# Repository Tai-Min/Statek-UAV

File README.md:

# Statek-UAV
ROS based UAV, Master's degree final project.

This repository consists of CAD files for the chassis, CAD files for electronic boards, catkin workspace for all ROS nodes created for the project and some additional scripts used during development.

The core part of this project is the real, 3D printed vehicle along with all the hardware attached to it (Jetson Nano B01 for main controller and STM32f103RBT6 for real time core). 

The software part of this project can be split into real time (closed loop wheel control), short term navigation (movement between two GPS waypoints) and long term navigation (navigation through series of GPS waypoints).
During the project's development, my main focus was on short term navigation, which is also the biggest and most complicated part of the project. Short term navigation stack
consists of static local map generator, dynamic local map generator (human leg detector mostly based on U-Net fully convolutional neural network), Voronoi graph generator, A* path planner and non linear model predictive controller for navigation.

For more info see [this arcitle](https://www.hackster.io/Tai-Min/statek-uav-ff225e).

**Just to warn you:** If you want to use this project somehow, use it as reference only. It is NOT meant to be assembled as it contains some design flaws both in hardware
and software that I don't intent to fix in this iteration of the project as code in this repository will stay in unchanged since the moment I handed over my thesis.
Most of the files in the "instructions" folder consists of the steps I've did to setup my hardware and Ipopt solver. Those might not work for you/could be dangerous (I might've abused sudo a bit) so use them at your own risk. The code quality depends on the time I had untill the deadline to hand over my thesis. In my opinion it should be fine for the most part, well documented and easy to follow but judge for yourself.

**Disclaimer:** I've tried to credit all authors of 3D files used in the project. All of the models had permissive license allowing me to use them.
If you see your work here without being credited or you just don't want to have your files used here - open an issue on this project and I'll fix any problems.

The files in this folder have the following structure:
* CAD
  * detailed - Inventor files for the 3D printing and assembling.
  * low_poly - Inventor files for simple low poly model for Gazebo and Rviz.
* catkin_ws/src
  * statek - Metapackage for the project
  * statek_calibrate - Calibration algorithms for cameras, GPS Kalman filter, IMU, Motor's PI controller autotuning. 
  * statek_config - Config files for the robot, including transformations, urdf and parameters for ROS nodes.
  * statek_hw - code to launch hardware based nodes (lidar, rosserial, cameras etc.) along with source code for real time controller.
  * statek_map - Mapping algorithms (dynamic local mapper, voronoi generator and GPS to hyperplane casting).
  * statek_ml - Leg detector based mostly on U-net fully convolutional neural network
  * statek_nav - Navigation algorithms (NMPC and GPS waypoint follower script).
  * statek_plan - A* path planner for short term navigation.
  * statek_playground - Simple launch nodes to play with the hardware.
  * statek_rviz - Rviz visualization files.
  * statek_sim - Gazebo simulation files.
  * statek_srv - Server files to communicate with web application (really rough draft).
  * statek_teleop - Teleoperation nodes for Dualshock 4 gamepad.
* electronics
  * AM4096_encoder - KiCad's files for AM4096 encoder board.
  * Nucleo_screw_shield - KiCad's files for screw shield that fits morpho connector.
  * button_panel - Unused in the project.
  * connections - Electrical connections of the project.
* instructions - Rough draft of what I did to setup the robot.
* media - Contains camera's calibration chessboard.
* thesis_scripts - Some files used to add more value to the project.

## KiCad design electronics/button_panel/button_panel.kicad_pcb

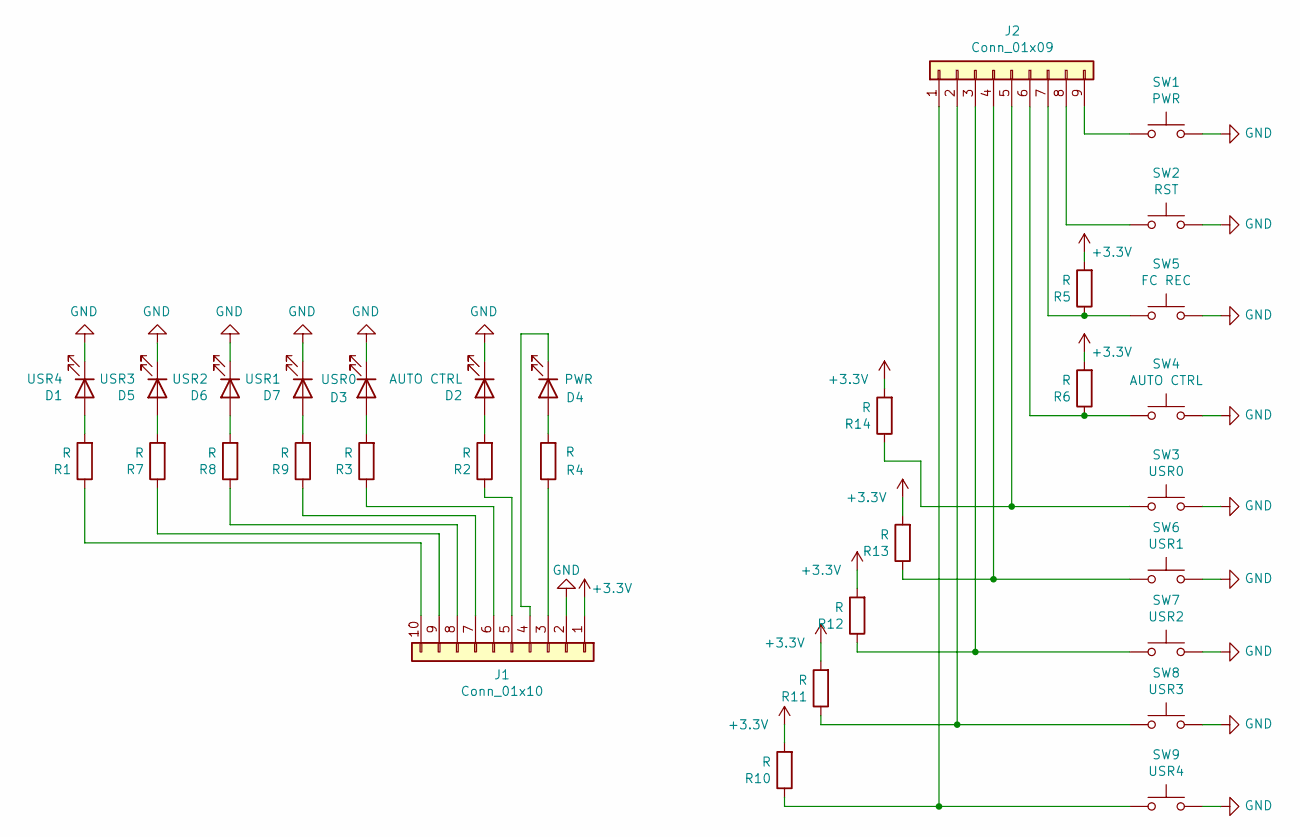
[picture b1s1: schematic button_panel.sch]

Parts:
D1: USR4; LED_D5.0mm_Clear
D2: AUTO CTRL; LED_D5.0mm_Clear
D3: USR0; LED_D5.0mm_Clear
D4: PWR; LED_D5.0mm_Clear
D5: USR3; LED_D5.0mm_Clear
D6: USR2; LED_D5.0mm_Clear
D7: USR1; LED_D5.0mm_Clear
J1: Conn_01x10; PinHeader_1x10_P2.54mm_Vertical
J2: Conn_01x09; PinHeader_1x09_P2.54mm_Vertical
R1, R2, R3, R4, R5, R6, R7, R8, R9, R10, R11, R12, R13, R14: R; R_1206_3216Metric_Pad1.42x1.75mm_HandSolder
SW1: PWR; SW_PUSH_6mm
SW2: RST; SW_PUSH_6mm
SW3: USR0; SW_PUSH_6mm
SW4: AUTO CTRL; SW_PUSH_6mm
SW5: FC REC; SW_PUSH_6mm
SW6: USR1; SW_PUSH_6mm
SW7: USR2; SW_PUSH_6mm
SW8: USR3; SW_PUSH_6mm
SW9: USR4; SW_PUSH_6mm

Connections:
+3V3: J1.1, R5.2, R6.2, R10.2, R11.2, R12.2, R13.2, R14.2
GND: D1.1 (K), D2.1 (K), D3.1 (K), D5.1 (K), D6.1 (K), D7.1 (K), J1.2, SW1.2, SW2.2, SW3.2, SW4.2, SW5.2, SW6.2, SW7.2, SW8.2, SW9.2
unnamed: D1.2 (A), R1.2
unnamed: D2.2 (A), R2.2
unnamed: D3.2 (A), R3.2
unnamed: D4.1 (K), J1.4
unnamed: D4.2 (A), R4.2
unnamed: D5.2 (A), R7.2
unnamed: D6.2 (A), R8.2
unnamed: D7.2 (A), R9.2
unnamed: J1.3, R4.1
unnamed: J1.5, R2.1
unnamed: J1.6, R3.1
unnamed: J1.7, R9.1
unnamed: J1.8, R8.1
unnamed: J1.9, R7.1
unnamed: J1.10, R1.1
unnamed: J2.1, R10.1, SW9.1
unnamed: J2.2, R11.1, SW8.1
unnamed: J2.3, R12.1, SW7.1
unnamed: J2.4, R13.1, SW6.1
unnamed: J2.5, R14.1, SW3.1
unnamed: J2.6, R6.1, SW4.1
unnamed: J2.7, R5.1, SW5.1
unnamed: J2.8, SW2.1
unnamed: J2.9, SW1.1

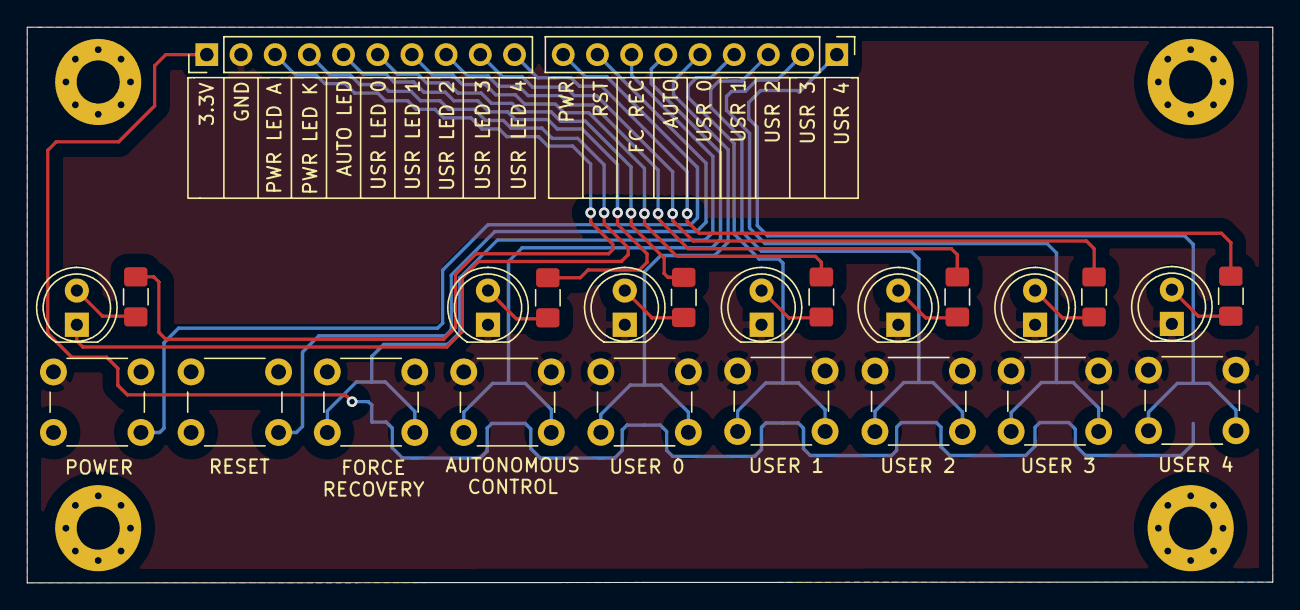
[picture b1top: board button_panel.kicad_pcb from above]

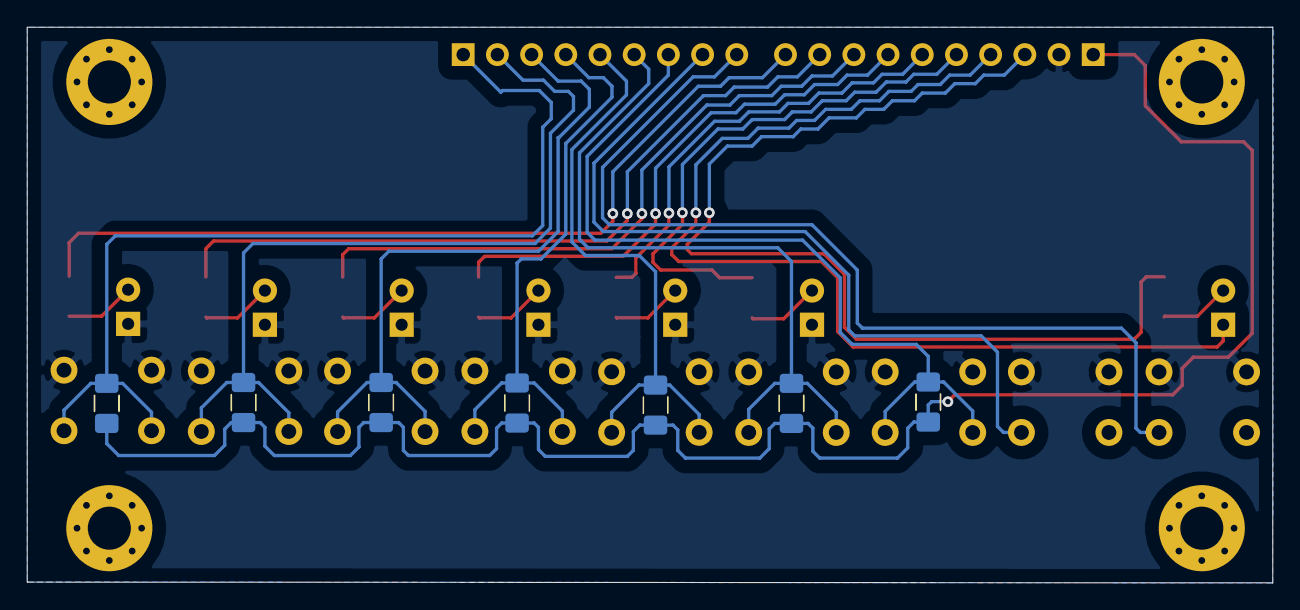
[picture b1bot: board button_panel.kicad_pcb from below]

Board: 2 copper layers, 92.5 x 41.3 mm, 32 parts (7 on the bottom side), 26 nets.

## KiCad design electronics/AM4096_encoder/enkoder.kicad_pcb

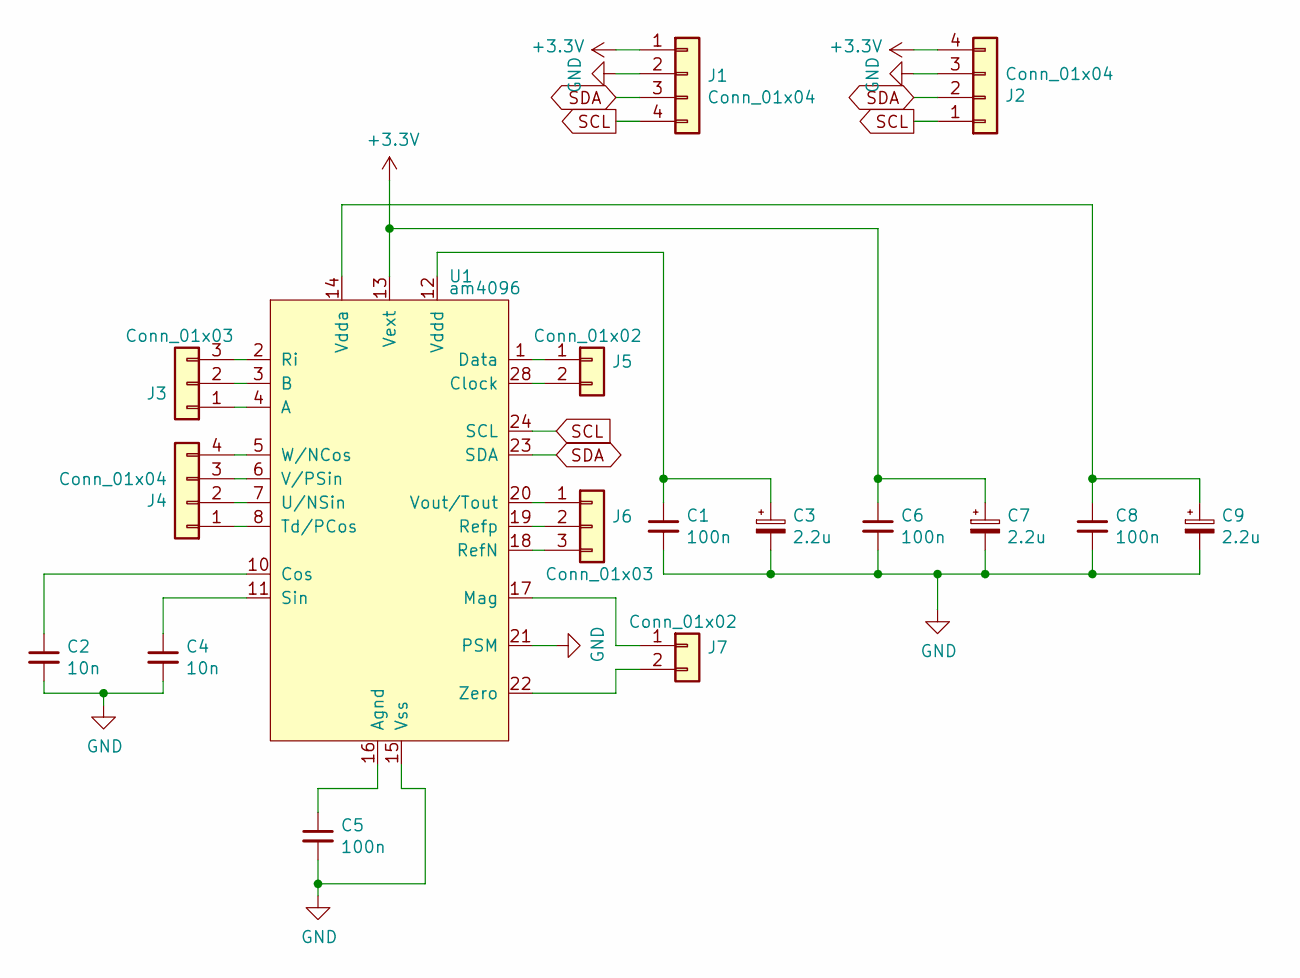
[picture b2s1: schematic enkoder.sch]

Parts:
C1, C5, C6, C8: 100n; C_1206_3216Metric_Pad1.42x1.75mm_HandSolder
C2, C4: 10n; C_1206_3216Metric_Pad1.42x1.75mm_HandSolder
C3, C7, C9: 2.2u; CP_EIA-3216-18_Kemet-A_Pad1.58x1.35mm_HandSolder
J1, J4: Conn_01x04; PinSocket_1x04_P2.54mm_Vertical
J2: Conn_01x04; TerminalBlock_MetzConnect_Type086_RT03404HBLC_1x04_P3.81mm_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
J3, J6: Conn_01x03; PinSocket_1x03_P2.54mm_Vertical
J5, J7: Conn_01x02; PinSocket_1x02_P2.54mm_Vertical
U1: am4096; SSOP-28_5.3x10.2mm_P0.65mm

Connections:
+3V3: C6.1, C7.1, J1.1, J2.4, U1.13 (Vext)
GND: C1.2, C2.2, C3.2, C4.2, C5.2, C6.2, C7.2, C8.2, C9.2, J1.2, J2.3, U1.15 (Vss), U1.21 (PSM)
unnamed: C1.1, C3.1, U1.12 (Vddd)
unnamed: C2.1, U1.10 (Cos)
unnamed: C4.1, U1.11 (Sin)
unnamed: C5.1, U1.16 (Agnd)
unnamed: C8.1, C9.1, U1.14 (Vdda)
unnamed: J3.1, U1.4 (A)
unnamed: J3.2, U1.3 (B)
unnamed: J3.3, U1.2 (Ri)
unnamed: J4.1, U1.8 (Td/PCos)
unnamed: J4.2, U1.7 (U/NSin)
unnamed: J4.3, U1.6 (V/PSin)
unnamed: J4.4, U1.5 (W/NCos)
unnamed: J5.1, U1.1 (Data)
unnamed: J5.2, U1.28 (Clock)
unnamed: J6.1, U1.20 (Vout/Tout)
unnamed: J6.2, U1.19 (Refp)
unnamed: J6.3, U1.18 (RefN)
unnamed: J7.1, U1.17 (Mag)
unnamed: J7.2, U1.22 (Zero)
SCL: J1.4, J2.1, U1.24 (SCL)
SDA: J1.3, J2.2, U1.23 (SDA)

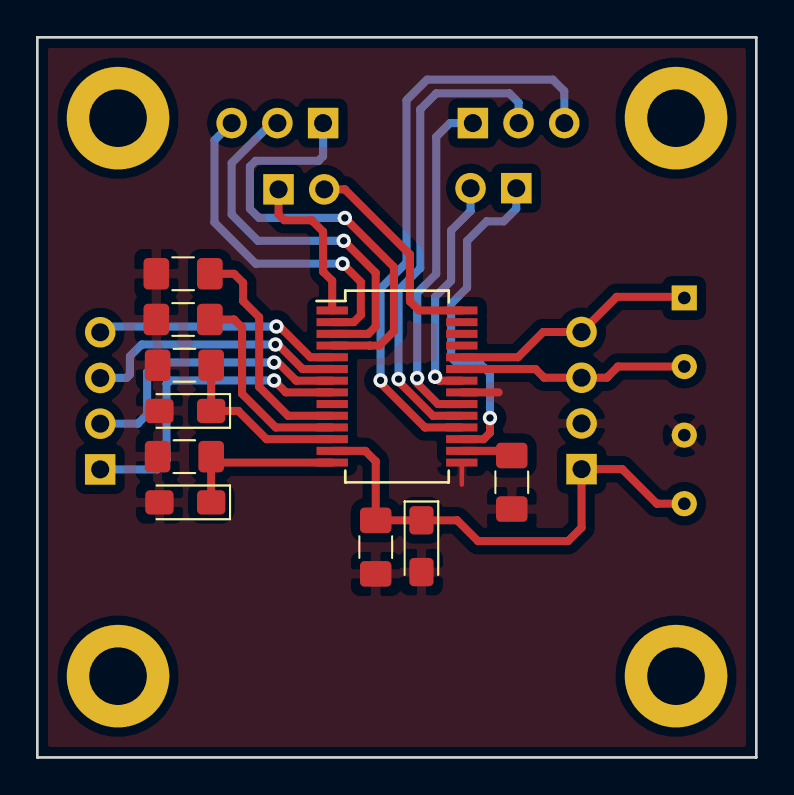
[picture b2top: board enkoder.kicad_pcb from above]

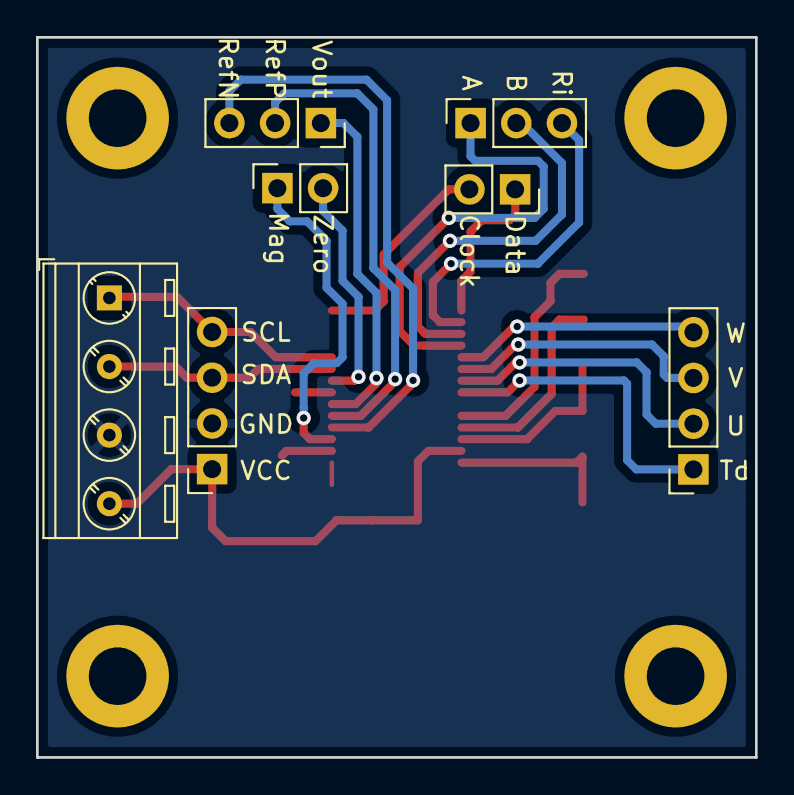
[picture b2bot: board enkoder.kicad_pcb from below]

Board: 2 copper layers, 39.9 x 40.0 mm, 21 parts (7 on the bottom side), 23 nets.

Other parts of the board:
 : MountingHole_3.2mm_M3_ISO7380_Pad
 #2,  #3,  #4: MountingHole_3.2mm_M3_ISO7380_Pad

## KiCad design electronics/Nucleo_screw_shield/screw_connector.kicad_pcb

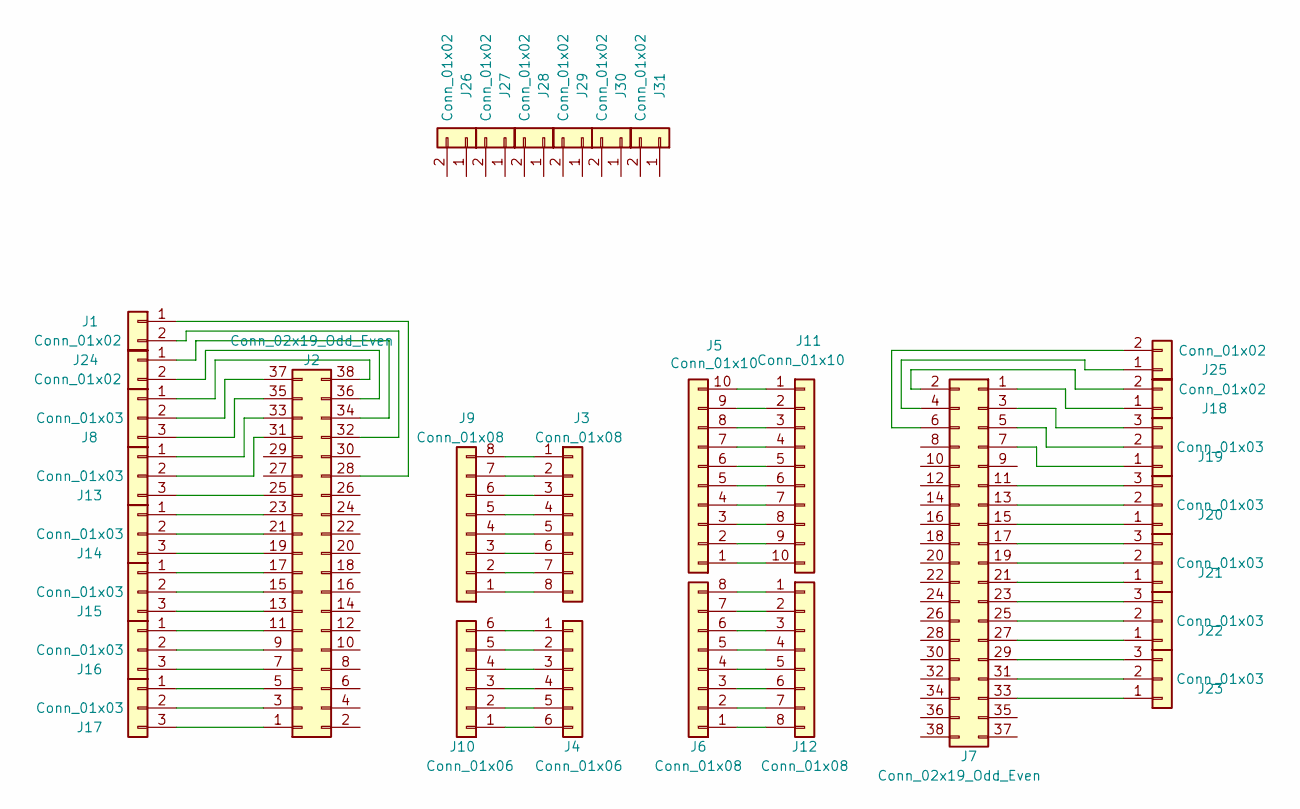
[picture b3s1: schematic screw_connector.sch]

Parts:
J1, J18, J24, J25, J26, J27, J28, J29, J30, J31: Conn_01x02; TerminalBlock_MetzConnect_Type086_RT03402HBLC_1x02_P3.81mm_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
J2, J7: Conn_02x19_Odd_Even; PinSocket_2x19_P2.54mm_Vertical
J3, J6: Conn_01x08; PinHeader_1x08_P2.54mm_Vertical
J4: Conn_01x06; PinSocket_1x06_P2.54mm_Vertical
J5: Conn_01x10; PinHeader_1x10_P2.54mm_Vertical
J8, J13, J14, J15, J16, J17, J19, J20, J21, J22, J23: Conn_01x03; TerminalBlock_MetzConnect_Type086_RT03403HBLC_1x03_P3.81mm_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
J9, J12: Conn_01x08; PinSocket_1x08_P2.54mm_Vertical
J10: Conn_01x06; PinHeader_1x06_P2.54mm_Vertical
J11: Conn_01x10; PinSocket_1x10_P2.54mm_Vertical

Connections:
unnamed: J1.1, J2.28
unnamed: J1.2, J2.32
unnamed: J2.34, J24.1
unnamed: J2.35, J8.3
unnamed: J2.36, J24.2
unnamed: J2.37, J8.2
unnamed: J2.38, J8.1
unnamed: J3.1, J9.8
unnamed: J3.2, J9.7
unnamed: J3.3, J9.6
unnamed: J3.4, J9.5
unnamed: J3.5, J9.4
unnamed: J3.6, J9.3
unnamed: J3.7, J9.2
unnamed: J3.8, J9.1
unnamed: J4.6, J10.1
unnamed: J4.5, J10.2
unnamed: J4.4, J10.3
unnamed: J4.3, J10.4
unnamed: J4.2, J10.5
unnamed: J4.1, J10.6
unnamed: J5.10, J11.1
unnamed: J5.9, J11.2
unnamed: J5.8, J11.3
unnamed: J5.7, J11.4
unnamed: J5.6, J11.5
unnamed: J5.5, J11.6
unnamed: J5.4, J11.7
unnamed: J5.3, J11.8
unnamed: J5.2, J11.9
unnamed: J5.1, J11.10
unnamed: J6.8, J12.1
unnamed: J6.7, J12.2
unnamed: J6.6, J12.3
unnamed: J6.5, J12.4
unnamed: J6.4, J12.5
unnamed: J6.3, J12.6
unnamed: J6.2, J12.7
unnamed: J6.1, J12.8
unnamed: J2.33, J13.1
unnamed: J2.31, J13.2
unnamed: J2.25, J13.3
unnamed: J2.23, J14.1
unnamed: J2.21, J14.2
unnamed: J2.19, J14.3
unnamed: J2.17, J15.1
unnamed: J2.15, J15.2
unnamed: J2.13, J15.3
unnamed: J2.11, J16.1
unnamed: J2.9, J16.2
unnamed: J2.7, J16.3
unnamed: J2.5, J17.1
unnamed: J2.3, J17.2
unnamed: J2.1, J17.3
unnamed: J7.1, J18.1
unnamed: J7.2, J18.2
unnamed: J7.7, J19.1
unnamed: J7.5, J19.2
unnamed: J7.3, J19.3
unnamed: J7.15, J20.1
unnamed: J7.13, J20.2
unnamed: J7.11, J20.3
unnamed: J7.21, J21.1
unnamed: J7.19, J21.2
unnamed: J7.17, J21.3
unnamed: J7.27, J22.1
unnamed: J7.25, J22.2
unnamed: J7.23, J22.3
unnamed: J7.33, J23.1
unnamed: J7.31, J23.2
unnamed: J7.29, J23.3
unnamed: J7.4, J25.1
unnamed: J7.6, J25.2

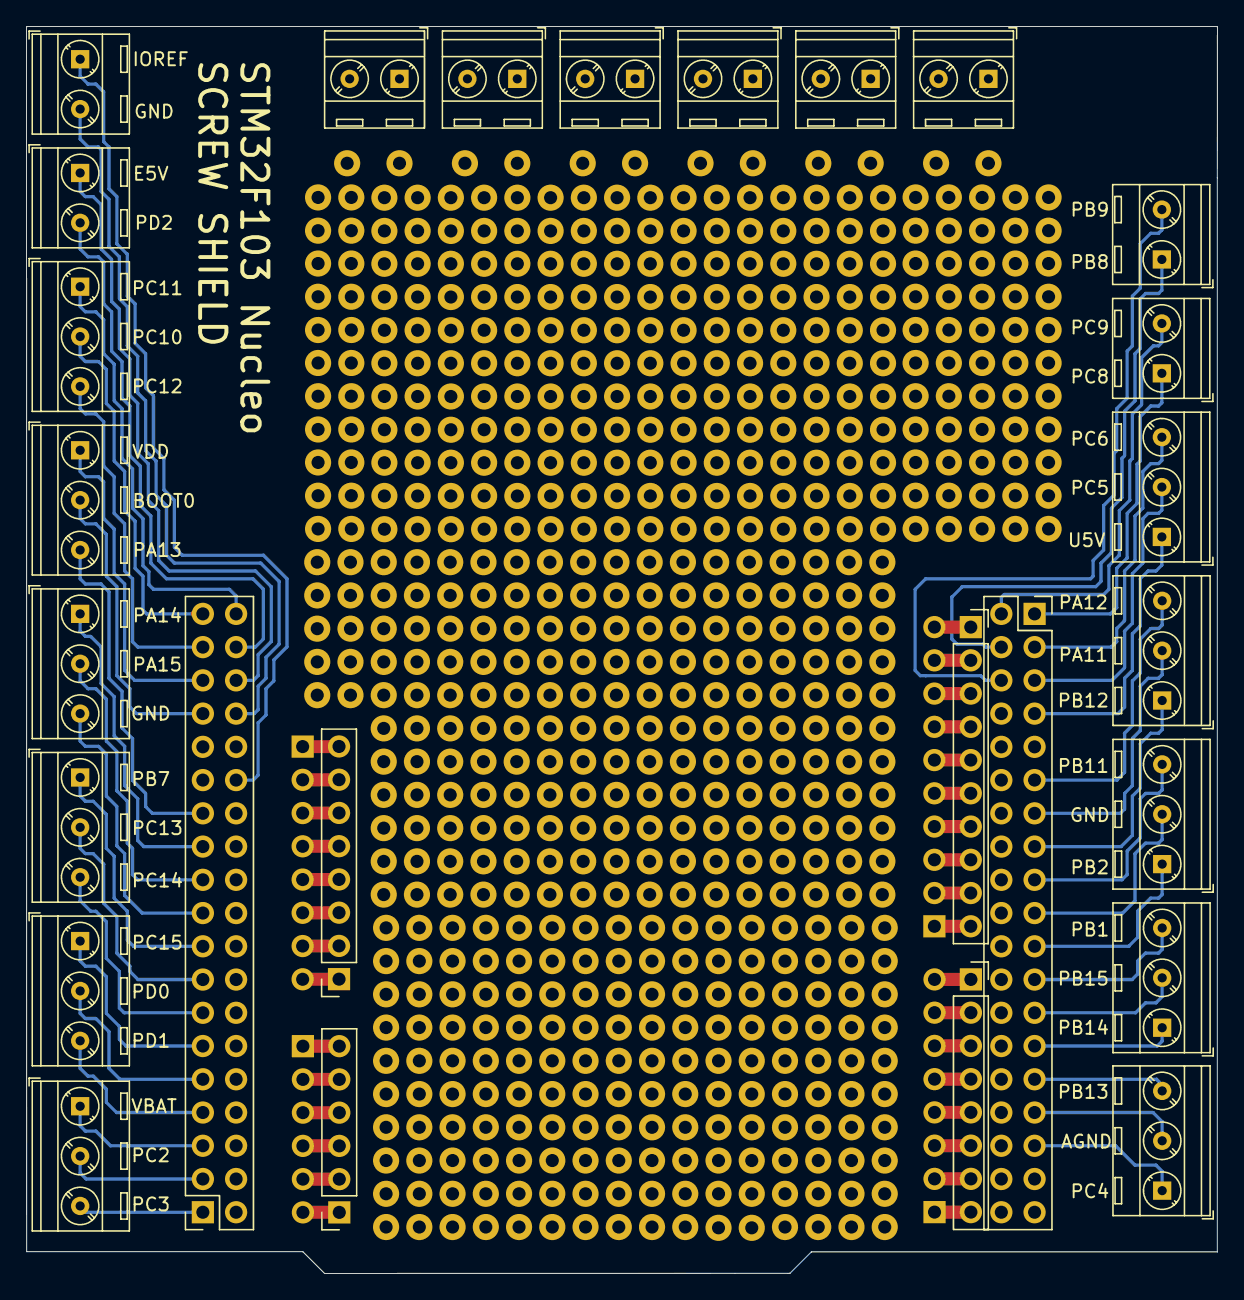
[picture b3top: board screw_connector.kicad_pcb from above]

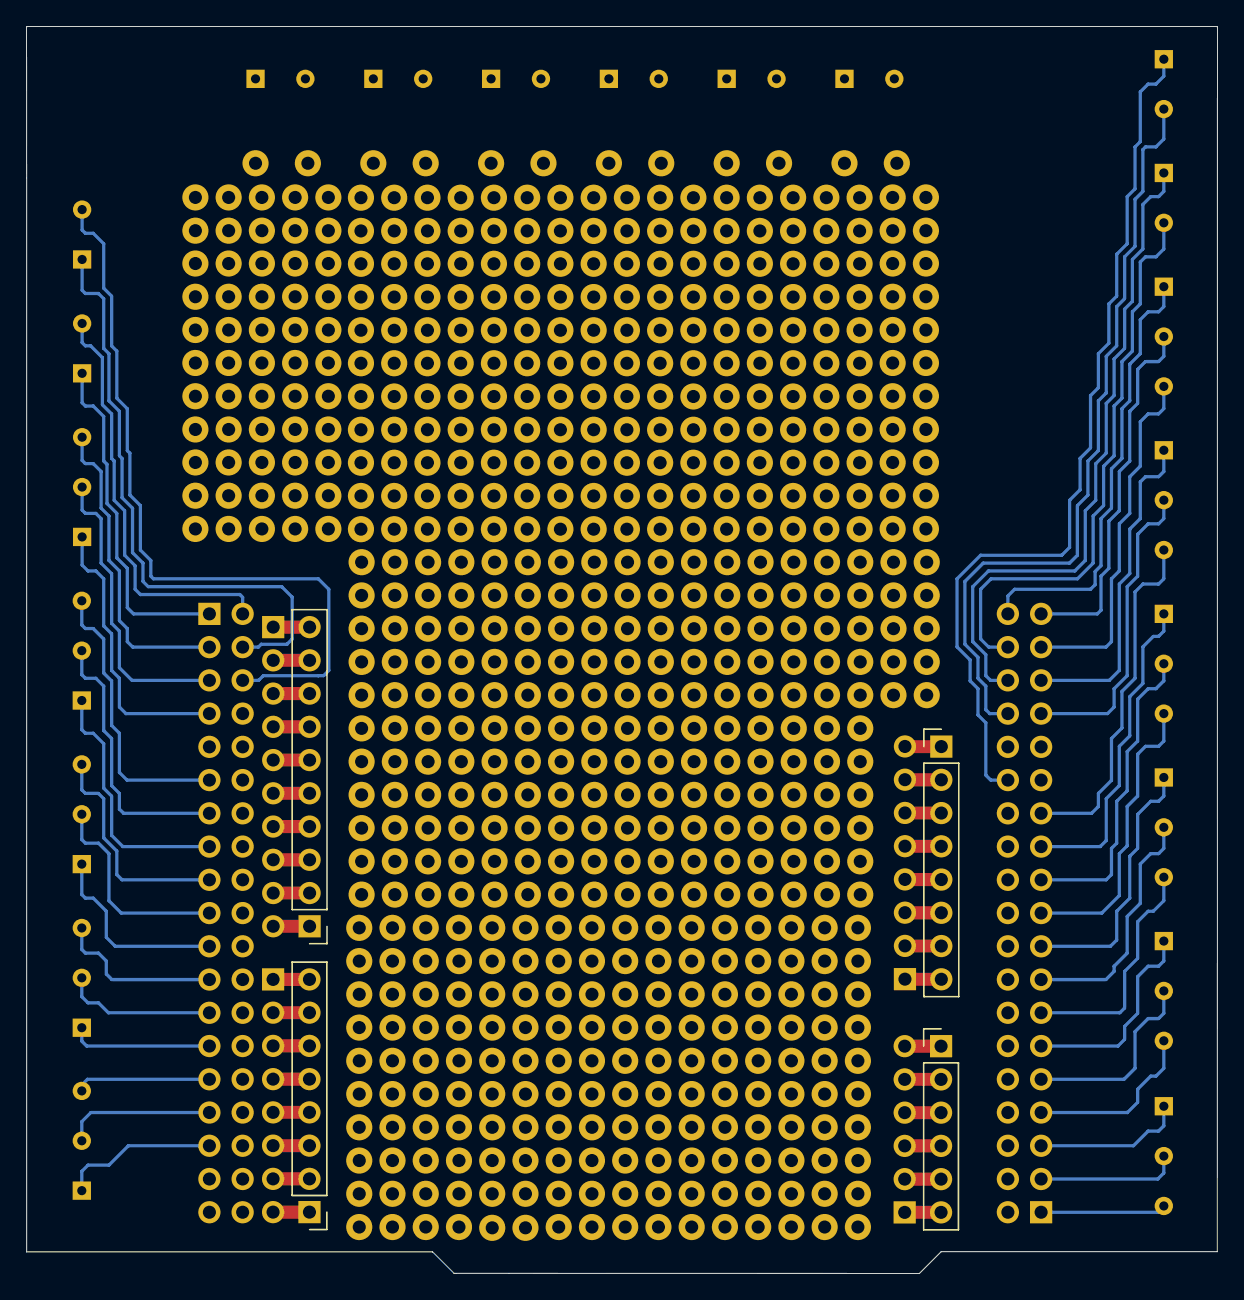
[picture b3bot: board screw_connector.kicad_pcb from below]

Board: 2 copper layers, 91.0 x 95.3 mm, 31 parts (4 on the bottom side), 73 nets.

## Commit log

2020-12-22 Reorganize CAD files
2020-12-22 Add tf, rviz, hw packages. Add lidar
2020-12-23 rename hardware.launch to statek.launch
2020-12-23 Add missing .iam files for thirdparty folder
2020-12-23 Markdown table test
2020-12-24 Add mesh to statek_rviz
2020-12-24 Edit assembly.iam
2020-12-24 Format README's
2020-12-24 Work on launch files, add xyz args to spawn_statek.launch
2020-12-24 Change from sdf to urdf
2020-12-24 Update readmes
2020-12-25 Edit dae urdf model
2020-12-25 Finish screw shield
2020-12-25 Finish AM4096 encoder board
2020-12-25 Remove unnecessary gerber files
2020-12-25 Remove datasheets and pdfs from encoder folder
2020-12-26 Add Encoder message, fix .gitignore to include ros package.xml files, cleanup package.xml and CMakeLists.txt
2020-12-26 Fix .gitignore
2020-12-26 Add encoder publishers, fix URDF links and joints, add code to dynamic transform publisher
2020-12-30 Rename start_here.md to main.md
2020-12-30 Working on vision_publisher_node
2020-12-30 Add visual_publisher_node and calibration file
2020-12-31 Reformat instruction
2021-01-10 Add multiple cameras to Gazebo
2021-01-10 Change CAD, add gerber zip files for electronics
2021-01-13 Update instructions, add imu cad, add gearing cad
2021-01-13 Add encoder cover
2021-03-01 Add button panel, edit CAD models
2021-03-07 Add battery basket and motor gearing CAD models
2021-03-07 Update instructions a bit
2021-03-07 Add connections schematic
2021-03-07 Add rosserial
2021-03-07 Add statek_rt
2021-03-08 Add cpp vision node with image transport
2021-03-08 Change rviz visualisation.
2021-03-08 Remove unnecessary files
2021-03-09 Add battery config
2021-03-09 Fix vision node service
2021-03-09 Modify camera calibration launch file
2021-03-09 Add depth calibrator
2021-03-09 Fix stereo_image_proc, change lidar's tf
2021-03-09 Work on camera calibrator
2021-03-10 Fix urdf a bit, update real time code
2021-03-10 Edit rviz
2021-03-10 Change motor control plugin
2021-03-10 Change rviz, change encoder transform publisher
2021-03-10 Working on wheel stabilizer
2021-03-10 Add velocity tester to RT code
2021-03-16 Edit button panel, edit CAD, add motor tensioners
2021-03-27 Add motion calibrator
2021-03-27 Remove namespace from test.launch
2021-03-27 Work on real time core
2021-03-27 Remove Kalman hpp/cpp
2021-03-27 Add chain guide models
2021-03-31 Add fake inertia
2021-03-31 Cleanup in launch files, move statek_rt into statek_hw
2021-03-31 Change some launch files
2021-03-31 Add name to config
2021-03-31 Add tf to statek_config, change Encoder msg
2021-04-01 Replace integral control with pid control
2021-04-01 Working on real time hardware
2021-04-02 Abandon mbed / gcc4mbed as it does not work with rosserial at all D:, switch to platrofmio and arduino
2021-04-02 to merge
2021-04-02 Change motion config from state space to pid
2021-04-03 Add imu stuff, change platformio upload script a bit
2021-04-03 Add real time param sender
2021-04-05 Add step response service
2021-04-08 Add odometry
2021-04-08 Change real time param sender
2021-04-08 Change connections
2021-04-08 Fix step response identification, change some messages
2021-04-09 Working on real time core, split step response identification service
2021-04-10 Syncing workspaces
2021-04-10 Add PID autotuning
2021-04-10 Add imu and odom to param sender node
2021-04-11 Add smoothing factor to motor params
2021-04-11 Finish real time core (hopefully)
2021-04-22 Sync with repo
2021-04-22 Move statek_tf and statek_msg packages to statek_hw
2021-04-23 Add local mapper cpp, add map to 3d markers
2021-04-24 Fix odometry compensation in mapper, add tf from sensor to footprint from mapper, add differential_to_twist_feedback node
2021-04-24 Add lidar to img node
2021-04-26 Fix motor control plugin
2021-04-26 Fix gazebo package
2021-04-26 Fix missing deps in statek_sim
2021-04-26 Change rviz a bit
2021-04-26 changed rviz a bit
2021-04-26 Fix imu linear acceleration reading.
2021-04-26 Fix odometry
2021-04-26 Change rviz file a bit
2021-04-26 Add PeTra network
2021-04-26 Add lidar dataset collector
2021-04-29 Change IMU param message
2021-04-29 Change imu params message
2021-04-29 Fix rayTrace in statek_map
2021-04-29 Change map size, placed BOLD line drawing stuff before obstacle detection in raytrace in statek's local mapper, amplified PID values a bit in optimizer.
2021-04-29 Fix python imports
2021-04-29 Change set imu params
2021-04-29 Sync workspace
2021-04-29 Fix problem with IMU set_param service
2021-04-29 Fix problem with IMU set_params service
2021-05-03 Add gps to tf node (empty for now)
2021-05-03 Add voronoi mapper node
2021-05-12 Work on voronoi mapper, cleanup in folders, sync all workspaces
2021-05-12 Add GPS to tf node
2021-05-12 Cleanup gps to tf node
2021-05-12 Fix map to markers node
2021-05-18 Add voronoi messages
2021-05-19 Add enu to geodetic in geo_to_tf_node
2021-05-19 Add Kalman filter to gps_to_tf_node
2021-05-19 Change IMU update rate
2021-05-19 Update IMU ASAP, Change real time messages to float32 instead of float64
2021-05-19 Add some compile flags for ubuntu to recognize M_PIf128
2021-05-27 Add connections to voronoi mapper, add voronoi visualization in Rviz
2021-05-27 Remove couts in gps_to_tf node
2021-05-27 Sync
2021-06-16 Add short term planner
2021-06-16 Work on voronoi graph generator
2021-06-16 Fix rotation in AbstractMap
2021-06-24 Add Ipopt to MPC code
2021-06-24 Remove unnecessary folders
2021-07-14 Add MPC code, set infinity as no goal value in voronoi map, comment Kalman filter in GPS to tf node for now, fix some launch files, split statek_hw into some clearly distinguished launch files, chang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
2021-07-14 Add park map, force rviz markers to be visible until next update, work a bit with Gazebo urdf model
2021-07-17 Fix nantransform in gps to tf node, change yaml configs a bit, tune mpc weights, add dynamic prediction horizon algorithm, move getTransform to separate thread in mpc and mappers for performance gains
2021-07-18 Update update mechanism in MPC, add mechanism to prevent stuck in some cases, change frame from map link to earth in short term planner node, change yaml configs
2021-07-25 Add gps data collector
2021-07-27 Change IMU in real time source
2021-08-09 Change imu angle reading in rt core
2021-08-12 Edit network and make it converge
2021-08-12 Add testing script for petranet
2021-08-13 Fine tune petranet
2021-08-13 Add real data preprocessor
2021-08-13 Add save_model.py to petranet
2021-08-13 General changes and bug fixing
2021-08-13 Add leg detector, change urdf a bit
2021-08-13 Working on leg detector
2021-08-17 Add queue_size for rospy subscribers where it was missing, work on leg_detector node, add lidar_img_config.yaml
2021-08-17 Change test.py in statek_ml
2021-08-18 Add bresenham filling to lidar_to_img node, add kalman filtering to leg_detector
2021-08-18 Retrain network
2021-08-18 Edit laser_to_img config
2021-08-18 Add build function to save_model.py
2021-08-18 Restore previous network model
2021-08-19 Work on leg detector
2021-08-19 Rework petranet model a bit
2021-08-19 Fix network model again ._. (not sure what happened)
2021-08-19 Make petranet smaller
2021-08-19 Cleanup petranet
2021-09-02 Change yaml configs, change process and measurement variance to matrices in fix_to_tf, working on leg detector, remove ROS_WARN from MPC node
2021-09-02 Retrained lidar network
2021-09-13 Move bresenham to abstract map, fuse static and dynamic maps, tune gps kalman, fix long term navigator
2021-09-13 Change sim and urdf
2021-09-25 Add thesis scripts
2021-11-07 Cleanup old readmes
2021-11-07 Create LICENSE
